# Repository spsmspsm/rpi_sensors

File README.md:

# rpi_sensors
#
# A small schematic / PCB design for a sensor interface for the Raspberry Pi 3

# DH11 Temp / Humidity probes
#
# HAN port combined w DH11 sensor interface:
# TODO: 24V -> 5V supply ??
# Data isolators for the sensors so that accidental 24V connections cannot kill the RPI

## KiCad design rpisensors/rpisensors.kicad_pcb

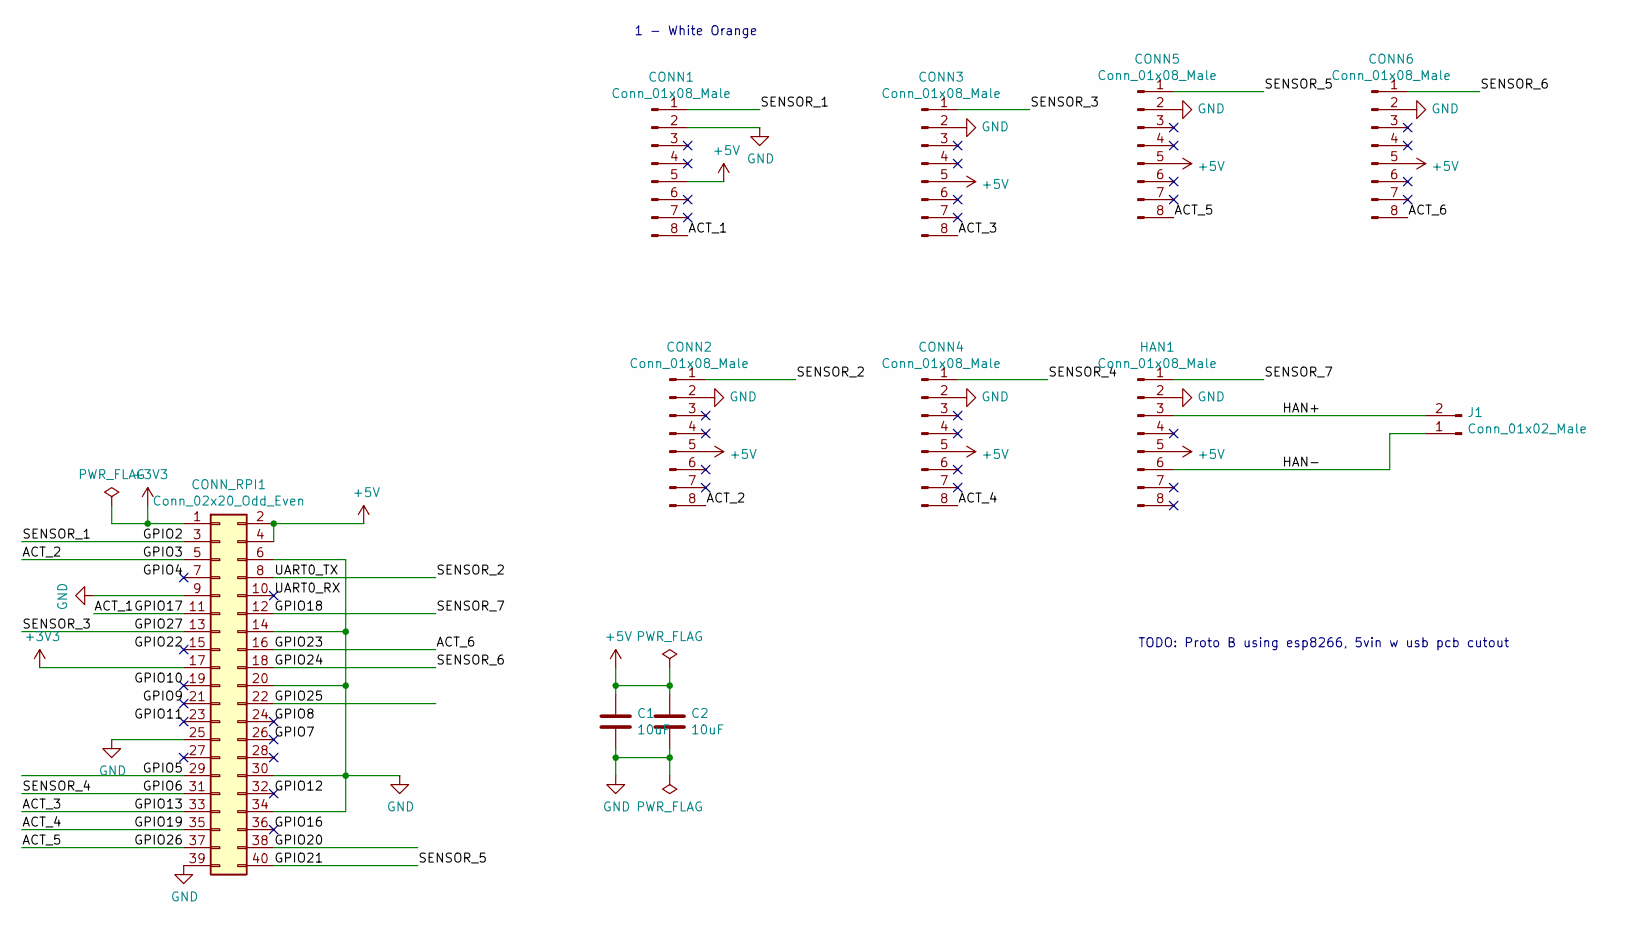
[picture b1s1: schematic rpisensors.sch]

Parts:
C1, C2: 10uF; CP_Radial_D5.0mm_P2.50mm
CONN1, CONN2, CONN3, CONN4, CONN5, CONN6: Conn_01x08_Male; RJ45_8_Stewart_2891016
CONN_RPI1: Conn_02x20_Odd_Even; Pin_Header_Straight_2x20_Pitch2.54mm
HAN1: Conn_01x08_Male; RJ45_8_Stewart_2891016
J1: Conn_01x02_Male; PINHEAD1-2

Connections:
+3V3: CONN_RPI1.1, CONN_RPI1.17
+5V: C1.1, C2.1, CONN1.5, CONN2.5, CONN3.5, CONN4.5, CONN5.5, CONN6.5, CONN_RPI1.2, CONN_RPI1.4, HAN1.5
/ACT_1: CONN1.8, CONN_RPI1.11
/ACT_2: CONN2.8, CONN_RPI1.5
/ACT_3: CONN3.8, CONN_RPI1.33
/ACT_4: CONN4.8, CONN_RPI1.35
/ACT_5: CONN5.8, CONN_RPI1.37
/ACT_6: CONN6.8, CONN_RPI1.16
/GPIO2: CONN1.1, CONN_RPI1.3
/GPIO4: CONN_RPI1.7
/GPIO5: CONN_RPI1.29
/GPIO6: CONN4.1, CONN_RPI1.31
/GPIO7: CONN_RPI1.26
/GPIO8: CONN_RPI1.24
/GPIO9: CONN_RPI1.21
/GPIO10: CONN_RPI1.19
/GPIO11: CONN_RPI1.23
/GPIO12: CONN_RPI1.32
/GPIO16: CONN_RPI1.36
/GPIO18: CONN_RPI1.12, HAN1.1
/GPIO20: CONN_RPI1.38
/GPIO21: CONN5.1, CONN_RPI1.40
/GPIO22: CONN_RPI1.15
/GPIO24: CONN6.1, CONN_RPI1.18
/GPIO25: CONN_RPI1.22
/GPIO27: CONN3.1, CONN_RPI1.13
/HAN+: HAN1.3, J1.2
/HAN-: HAN1.6, J1.1
/SENSOR_2: CONN2.1, CONN_RPI1.8
/UART0_RX: CONN_RPI1.10
GND: C1.2, C2.2, CONN1.2, CONN2.2, CONN3.2, CONN4.2, CONN5.2, CONN6.2, CONN_RPI1.6, CONN_RPI1.9, CONN_RPI1.14, CONN_RPI1.20, CONN_RPI1.25, CONN_RPI1.30, CONN_RPI1.34, CONN_RPI1.39, HAN1.2

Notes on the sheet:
1 - White Orange
TODO: Proto B using esp8266, 5vin w usb pcb cutout

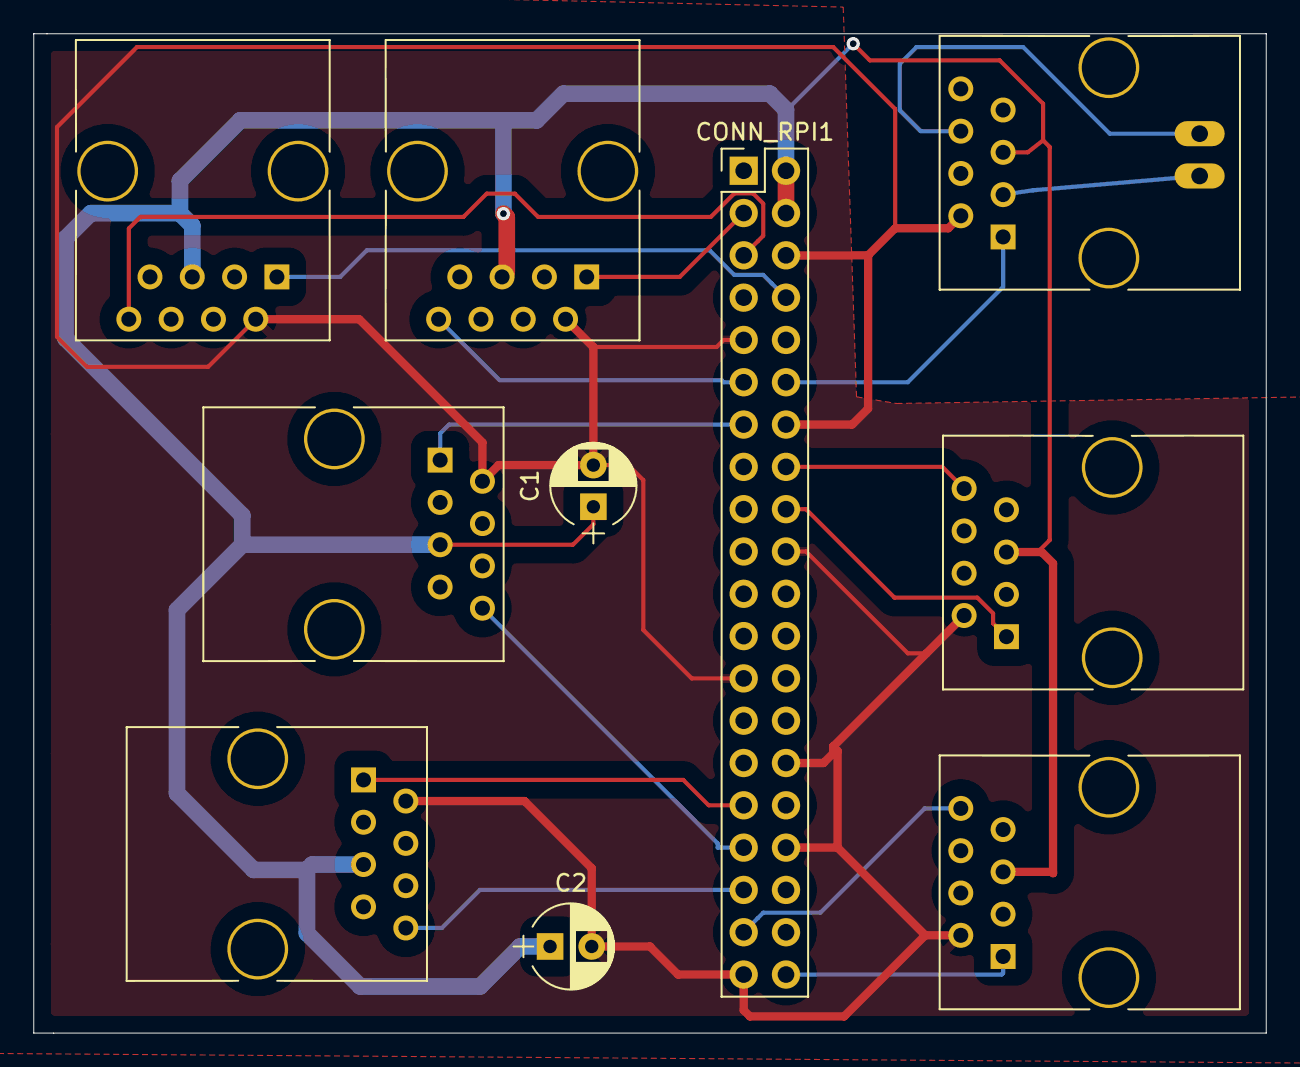
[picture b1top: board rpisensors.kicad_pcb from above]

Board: 2 copper layers, 74.0 x 60.0 mm, 11 parts (1 on the bottom side), 18 nets.

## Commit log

2020-05-10 First draft
2020-05-12 Added wiring. Lacks silkscreen and final touch
